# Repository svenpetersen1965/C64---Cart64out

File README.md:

# C64---Cart64out
Cart64out is a breakout board for the Commodore C64 Expansion Port 

All signals of the C64 expansion port are connected to a box pin header. This way, they can be displayed 
with a logic analyzer or an oscilloscope. A helpful feature for analysing the functionality for a cartridge.
Some configuration and chip select signals are connected to a jumper, hence they can be interrupted by pulling 
a jumper, which might be useful for copying a cartridge. To provide a perfect timing for this, a micro controller 
could be connected to the Jumper JP1.

Also the signals from J2 can be connected to a bread board. The two GND and two +5V pins on JP1 are intended for this purpose.

# Rev. 0a
This revision is a derivative of Rev. 0. It offers two additional mounting holes, in case this board is used to be an extension of the port (not tested, yet).

# Rev. 1
Rev. one has four mounting holes and additional signals (/IRQ , /NMI and /DMA) on the pin header JP1. 

# Calculation of the BOM
The compnent prices (PBC included) were summed up. The total costs are 2.99€ (depending on the part sourcing). No shipping fees are included.

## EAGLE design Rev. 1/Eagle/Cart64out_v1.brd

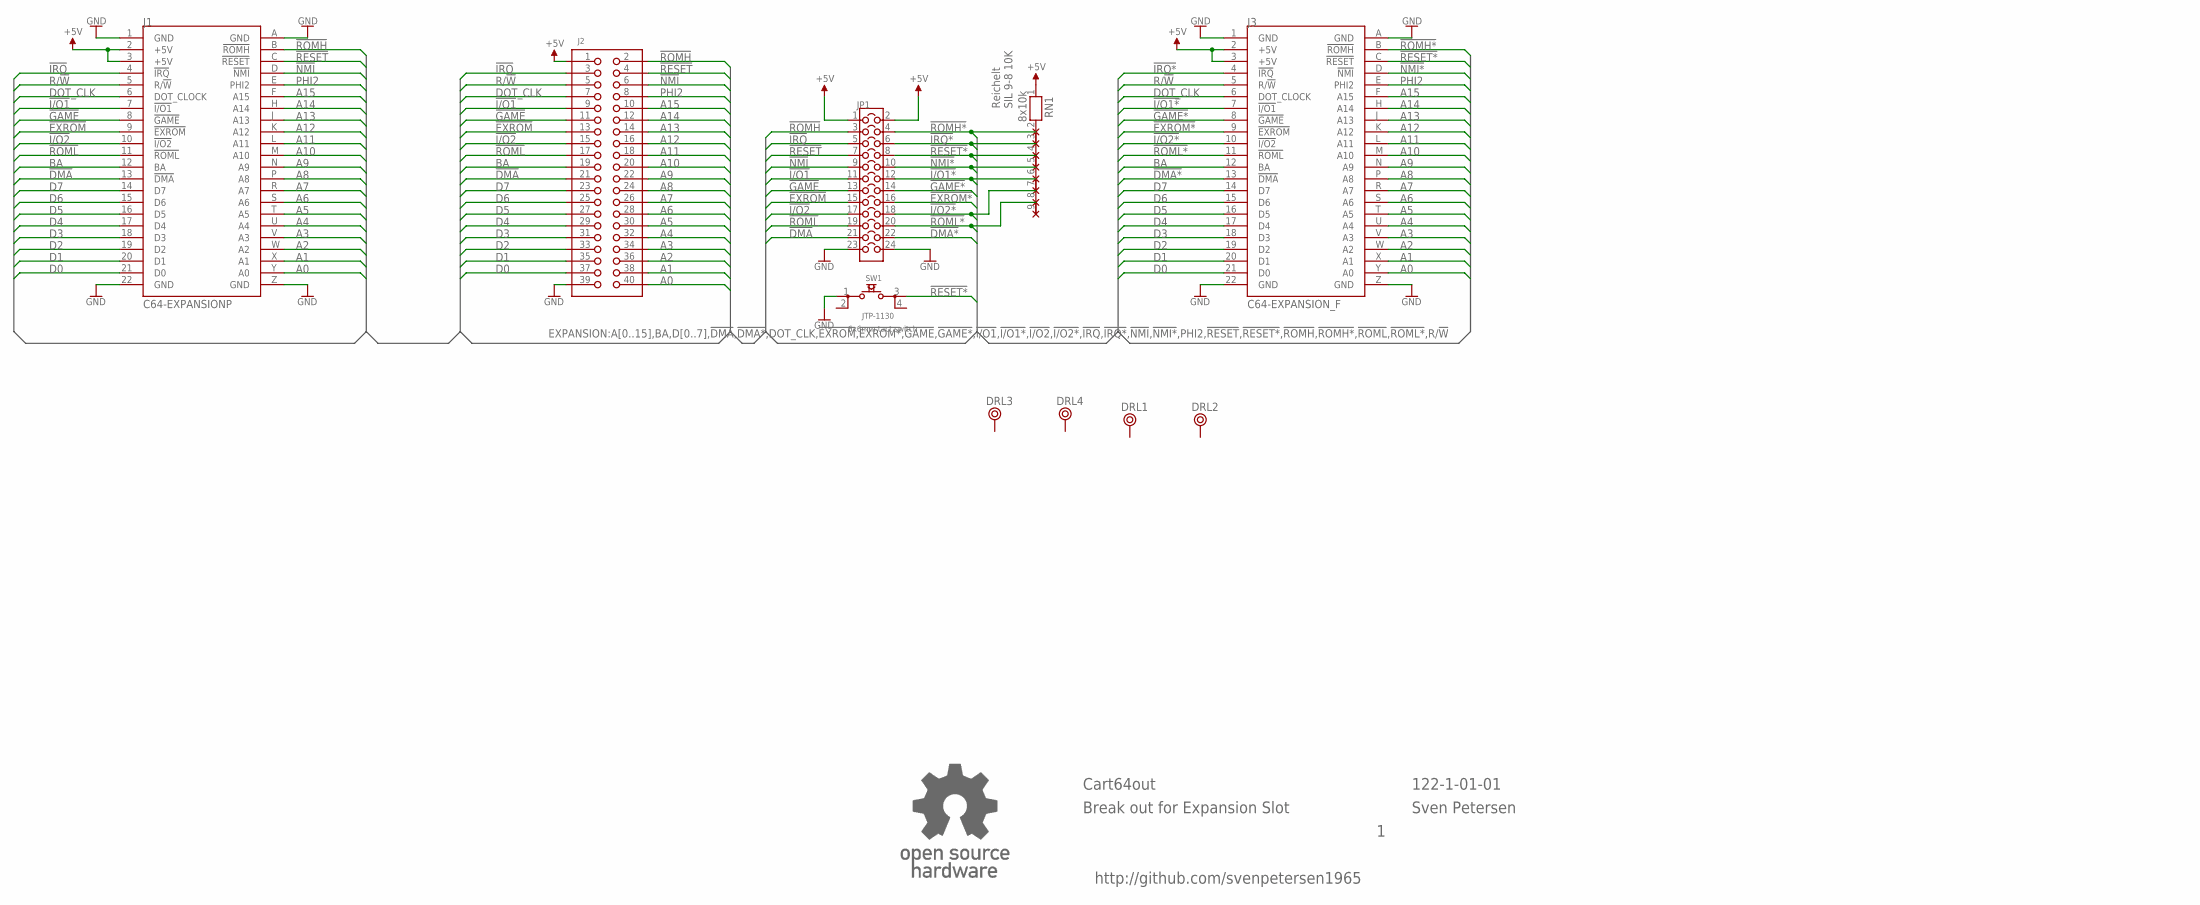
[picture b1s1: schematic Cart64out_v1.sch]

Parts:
DRL1, DRL2, DRL3, DRL4: BOHR3,3
J1: C64-EXPANSIONP; EXPPORT
J2: PINHD-2X20WV; 2X20WV
J3: C64-EXPANSION_F; EXPANSION_OUT
JP1: COMBI_2X12; COMBI-12X2
RN1: 8x10k; RN-9
SW1: JTP-1130
U$22: OPEN_SOURCE_HW; OPENHW

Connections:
!DMA: J1.13 (!DMA), J2.21, JP1.21
!DMA*: J3.13 (!DMA), JP1.22
!EXROM: J1.9 (!EXROM), J2.13, JP1.15
!EXROM*: J3.9 (!EXROM), JP1.16
!GAME: J1.8 (!GAME), J2.11, JP1.13
!GAME*: J3.8 (!GAME), JP1.14
!I/O1: J1.7 (!I/O1), J2.9, JP1.11
!I/O1*: J3.7 (!I/O1), JP1.12, RN1.6
!I/O2: J1.10 (!I/O2), J2.15, JP1.17
!I/O2*: J3.10 (!I/O2), JP1.18, RN1.7
!IRQ: J1.4 (!IRQ), J2.3, JP1.5
!IRQ*: J3.4 (!IRQ), JP1.6, RN1.3
!NMI: J1.D (!NMI), J2.6, JP1.9
!NMI*: J3.D (!NMI), JP1.10, RN1.5
!RESET: J1.C (!RESET), J2.4, JP1.7
!RESET*: J3.C (!RESET), JP1.8, RN1.4, SW1.3
!ROMH: J1.B (!ROMH), J2.2, JP1.3
!ROMH*: J3.B (!ROMH), JP1.4, RN1.2
!ROML: J1.11 (!ROML), J2.17, JP1.19
!ROML*: J3.11 (!ROML), JP1.20, RN1.8
+5V: J1.2 (+5V), J1.3 (+5V), J2.1, J3.2 (+5V), J3.3 (+5V), JP1.1, JP1.2, RN1.1
A0: J1.Y (A0), J2.40, J3.Y (A0)
A1: J1.X (A1), J2.38, J3.X (A1)
A2: J1.W (A2), J2.36, J3.W (A2)
A3: J1.V (A3), J2.34, J3.V (A3)
A4: J1.U (A4), J2.32, J3.U (A4)
A5: J1.T (A5), J2.30, J3.T (A5)
A6: J1.S (A6), J2.28, J3.S (A6)
A7: J1.R (A7), J2.26, J3.R (A7)
A8: J1.P (A8), J2.24, J3.P (A8)
A9: J1.N (A9), J2.22, J3.N (A9)
A10: J1.M (A10), J2.20, J3.M (A10)
A11: J1.L (A11), J2.18, J3.L (A11)
A12: J1.K (A12), J2.16, J3.K (A12)
A13: J1.J (A13), J2.14, J3.J (A13)
A14: J1.H (A14), J2.12, J3.H (A14)
A15: J1.F (A15), J2.10, J3.F (A15)
BA: J1.12 (BA), J2.19, J3.12 (BA)
D0: J1.21 (D0), J2.37, J3.21 (D0)
D1: J1.20 (D1), J2.35, J3.20 (D1)
D2: J1.19 (D2), J2.33, J3.19 (D2)
D3: J1.18 (D3), J2.31, J3.18 (D3)
D4: J1.17 (D4), J2.29, J3.17 (D4)
D5: J1.16 (D5), J2.27, J3.16 (D5)
D6: J1.15 (D6), J2.25, J3.15 (D6)
D7: J1.14 (D7), J2.23, J3.14 (D7)
DOT_CLK: J1.6 (DOT_CLOCK), J2.7, J3.6 (DOT_CLOCK)
GND: J1.1 (GND), J1.22 (GND), J1.A (GND), J1.Z (GND), J2.39, J3.1 (GND), J3.22 (GND), J3.A (GND), J3.Z (GND), JP1.23, JP1.24, SW1.1
PHI2: J1.E (PHI2), J2.8, J3.E (PHI2)
R/!W: J1.5 (R/!W), J2.5, J3.5 (R/!W)

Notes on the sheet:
Reichelt SIL 9-8 10K
Cart64out
Break out for Expansion Slot
Sven Petersen
122-1-01-01
http://github.com/svenpetersen1965
6x6mm tact switch

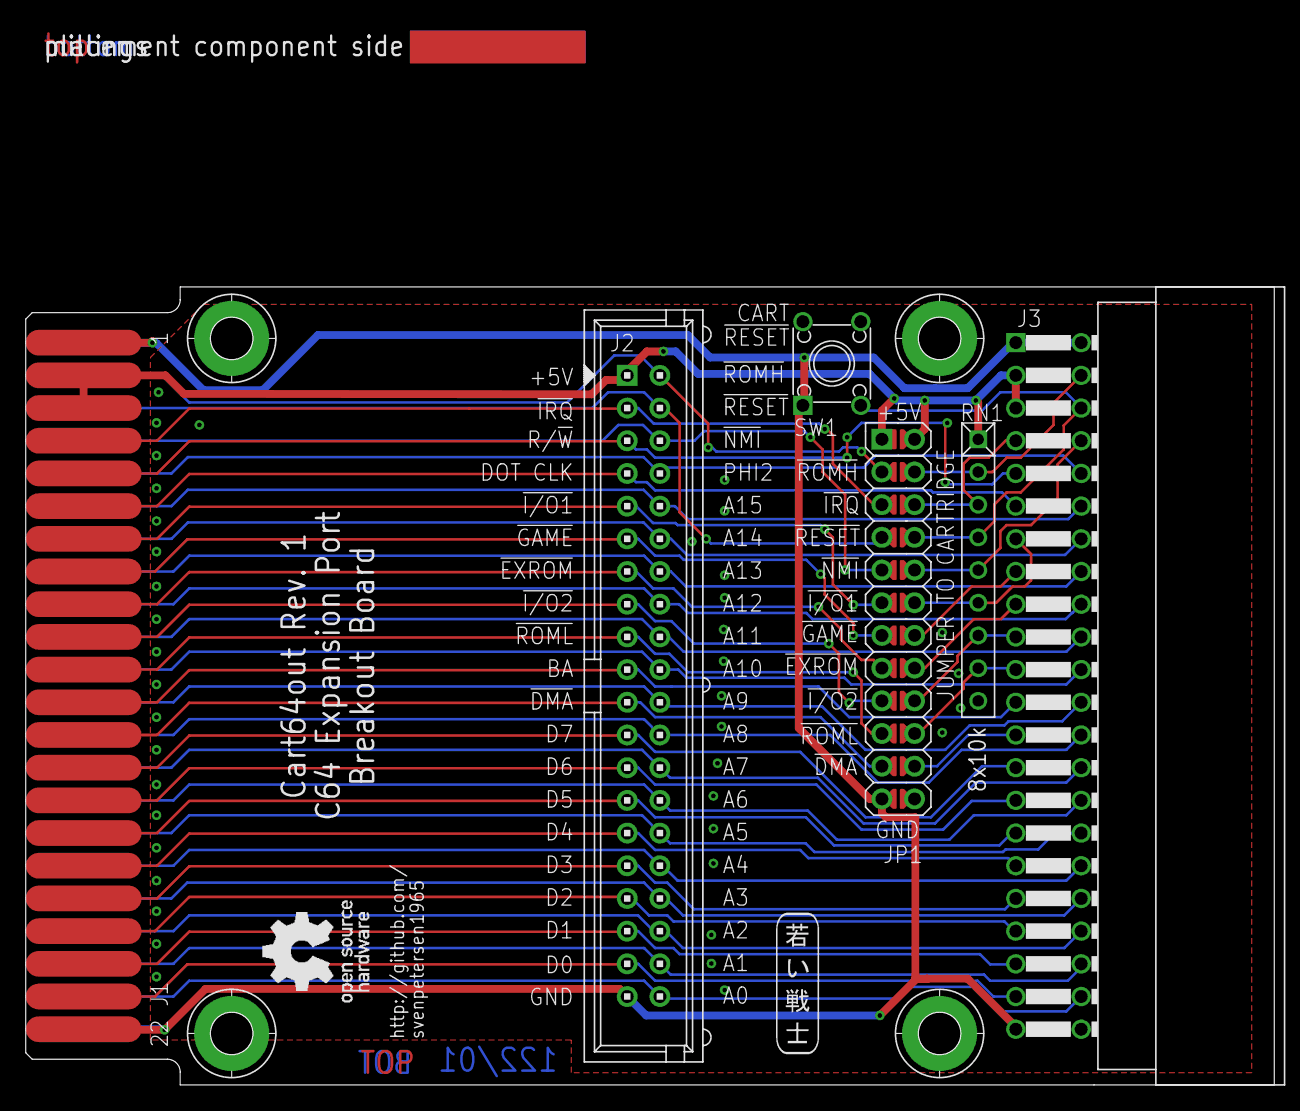
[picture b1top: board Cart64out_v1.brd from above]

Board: 2 copper layers, 96.9 x 82.2 mm, 14 parts (0 on the bottom side), 50 nets.

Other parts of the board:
U$20: 2LAYER
U$21: PCB-TITLE/
U$23: SVEN_TAG

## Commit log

2020-06-09 Calculation of BOM
    Component prices added
2020-08-10 Silk Screen Update
2021-11-16 Doc update
    new dimensions added to the drawing
2021-11-16 Doc Update
    New dimensions added
2021-11-16 dxf file new
2021-11-16 New dimensions added to the drawing
2022-02-08 Generated a version with four mounting holes
2022-10-29 Rev. 1 released
